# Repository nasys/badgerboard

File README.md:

___               _                      _                             _
				(  _`\            ( )                    ( )                           ( )
				| (_) )   _ _    _| |   __     __   _ __ | |_      _      _ _  _ __   _| |
				|  _ <' /'_` ) /'_` | /'_ `\ /'__`\( '__)| '_`\  /'_`\  /'_` )( '__)/'_` |
				| (_) )( (_| |( (_| |( (_) |(  ___/| |   | |_) )( (_) )( (_| || |  ( (_| |
			    (____/'`\__,_)`\__,_)`\__  |`\____)(_)   (_,__/'`\___/'`\__,_)(_)  `\__,_)
									 ( )_) |
								 	  \___/'
============================

### **Table of Contents**
 * [Prerequisites](#prerequisites)
 	* [Downloads](#downloads)
	* [General installation](#general-installation)
 	* [Mac OS X installation with Git](#mac-os-x-installation-with-git)
 	* [Windows installation with Git](#windows-installation-with-git)
 * [Badgerboard Setup](#badgerboard-setup)
	* [Test out your Badgerboard](#test-out-your-badgerboard) 
 	* [LoRa sensor setup](#lora-sensor-setup)
 * [Debugging](#debugging)
 * [Known issues](#known-issues)
 * [Version log](#version-log)
 * [Used libraries](#used-libraries)
 * [Licences](#licences)

### Prerequisites

##### Downloads

* [**Arduino**](https://www.arduino.cc/en/Main/Software)
* [**Git**](https://git-scm.com/book/en/v2/Getting-Started-Installing-Git)

#### General installation
* [Download](https://github.com/nasys/badgerboard/archive/master.zip) this library as **.zip** file

now this file is in downloads folder named Badgerboard-master.zip

* Open Arduino and include it under **Sketch -> Include library -> add .zip library**

##### Mac OS X installation with Git

* Open "**Finder**" (Press &#8984;+ Space ) 
* type in "terminal" and open it
* type "cd Documents/Arduino/libraries"
* type "git clone https://github.com/nasys/badgerboard"
* Now when you open up your Arduino and _Badgerboard_ library should appear under **Sketch -> Include library**

##### Windows installation with Git

Coming soon

### **Badgerboard setup**
#### Test out your Badgerboard
```diff
- DO NOT POWER ON WITHOUT ANTENNA! 

```

* Make sure Badgerboard power switch is turned ON ([button towards USB port](https://www.maker.io/-/media/makerio/makerimages/blogs/badgerboard/badgerboard-figure-1.jpg?la=en&hash=B2158C77D4DA2ACD35EAA878DF2E584F373AB571))
* connect Badgerboard to your PC/Mac 
* Open Arduino
* Open Blink example **Files -> Examples -> 01.Basics -> Blink**
* Make sure you have chosen correct board  **Tools -> Board -> LilyPad Arduino USB** and correct port **Tools -> Port** 
* Change the time(number in milliseconds) inside the brackets after "**delay**" to change the speed of blinking
* To **upload** click on the __right pointing arrow__ on the top-left corner of your Arduino window

In case all of this works then you have successfully uploaded your first program to Badgerboard

#### LoRa sensor setup

* Open **File -> Examples -> Badgerboard -> LoRa_temp_hum**
* Replace examples **devEUI**(16 hex char), **appEUI**(16 hex char) and **appKey**(32 hex char) with the ones that Your LoRaWAN™ solution provider has assigned.([example 1](#example-1)) 
* Upload Your code to Badgerboard

##### example 1

	In Arduino code your devEUI, appEUI and appKey are represented by char array and should look similar to 
	this example
	
	const uint8_t devEUI[8] = {
	0x11, 0x11, 0x22, 0x22,
	0x33, 0x33, 0x44, 0x44
	};

	const uint8_t appKey[16] = {
	0x11, 0x11, 0x11, 0x11,
	0x11, 0x11, 0x22, 0x22,
	0x22, 0x22, 0x22, 0x22,
	0x33, 0x33, 0x33, 0x33
	};

	const uint8_t appEUI[8] = {
	0x11, 0x22, 0x33, 0x44,
	0x55, 0x66, 0x77, 0x88
	};

### Debugging

To see Debugging messages open Serial Monitor **Tools -> Serial Monitor**
#### Known issues

* Take a look under [troubleshooting](https://github.com/nasys/badgerboard/wiki/Troubleshooting) page
* Works only with Arduino version 1.6.10 and later

### Version log

#### Version 0.0.3
	* Added a quickfix related to SF not changeing
	* Added _mod to library names to avoid issues if libraries are already installed
	
#### Version 0.0.2
:calendar:06.12.2016

	* Changed spreading factor changing to automatic
	* Added liquid detection example 

#### Version 0.0.1
:calendar:01.11.2016 

	Initial version of Badgerboard library

#### Used libraries
* [**FaBoHumidity_HTS221**](https://github.com/FaBoPlatform/FaBoHumidity-HTS221-Library)
* [**LowPower**](https://github.com/rocketscream/Low-Power)
* [**Sodaq_RN2483**](https://github.com/SodaqMoja/Sodaq_RN2483)

### **Licences**

All of the source files are distributed under the beerware license except where specified otherwise (i.e. external libraries)
 
#### Contacts
In case you found the instructions incomplete or have any questions regarding Badgerboard library
You can :
* Open new thread under [issues](https://github.com/nasys/badgerboard/issues)
* :e-mail: [contact us](mailto:badgerboard@nasys.no)

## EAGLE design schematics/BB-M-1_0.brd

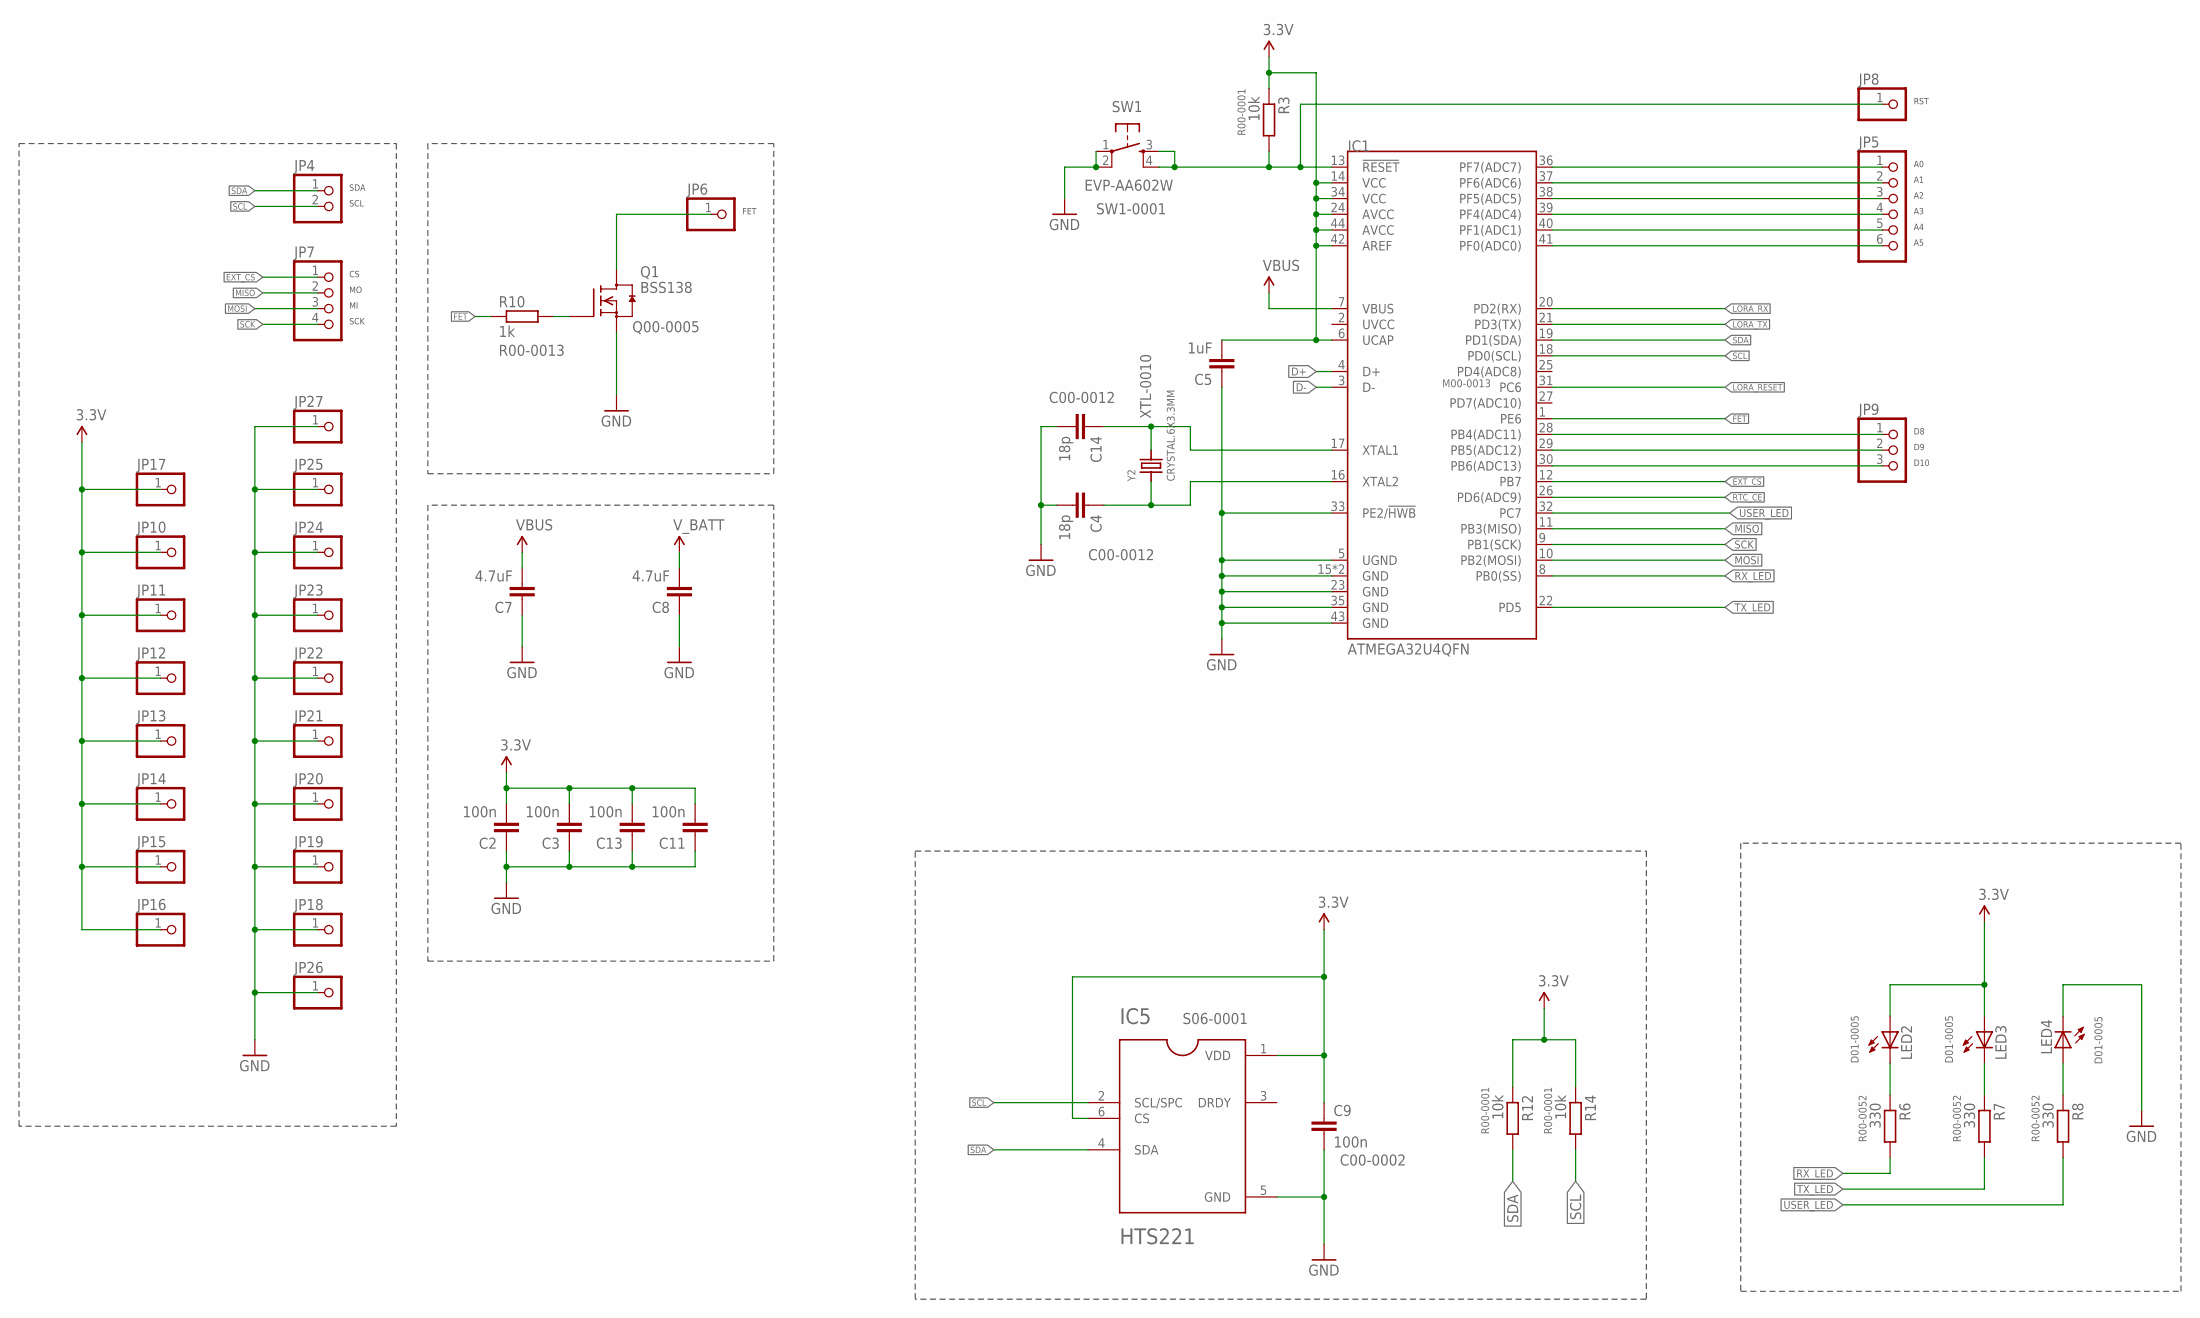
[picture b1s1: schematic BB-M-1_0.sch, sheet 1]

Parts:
C2, C3, C9, C11, C13: 100n; C0402
C4, C14: 18p; C0402
C5: 1uF; C0402
C7, C8: 4.7uF; C0603
IC1: ATMEGA32U4QFN; QFN-44
IC5: HTS221; LGA6R75P3X2_200X200X90
JP4: HEADER-1X2ROUND; 1X02_ROUND
JP5: HEADER-1X6ROUND; 1X06_ROUND
JP6, JP8, JP10, JP11, JP12, JP13, JP14, JP15, JP16, JP17, JP18, JP19, JP20, JP21, JP22, JP23, JP24, JP25, JP26, JP27: HEADER-1X1ROUND; 1X01_ROUND
JP7: HEADER-1X4ROUND; 1X04_ROUND
JP9: HEADER-1X3ROUND; 1X03_ROUND
LED2, LED3, LED4: LED0603; LED-0603
Q1: BSS138; SOT23
R3, R12, R14: 10k; R0402
R6, R7, R8: 330; R0402
R10: 1k; R0402
SW1: EVP-AA602W; UUS_BUTTON
Y2: CRYSTAL.6X3.3MM; 6X3.3MM

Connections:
3.3V: C2.2, C3.2, C5.2, C9.1, C11.2, C13.2, IC1.6 (UCAP), IC1.14 (VCC), IC1.24 (AVCC), IC1.34 (VCC), IC1.42 (AREF), IC1.44 (AVCC), IC5.1 (VDD), IC5.6 (CS), JP10.1, JP11.1, JP12.1, JP13.1, JP14.1, JP15.1, JP16.1, JP17.1, LED2.A, LED3.A, R3.1, R12.1, R14.1; also elsewhere on the board
5V: C7.2, IC1.7 (VBUS); also elsewhere on the board
D+: IC1.4 (D+); also elsewhere on the board
D-: IC1.3 (D-); also elsewhere on the board
EXT_CS: IC1.12 (PB7), JP7.1
FET: IC1.1 (PE6), R10.1
FET_OUTPUT: JP6.1, Q1.3 (D)
GND: C2.1, C3.1, C4.2, C5.1, C7.1, C8.1, C9.2, C11.1, C13.1, C14.2, IC1.5 (UGND), IC1.15 (GND), IC1.23 (GND), IC1.33 (PE2/!HWB), IC1.35 (GND), IC1.43 (GND), IC1.EPAD (GND), IC5.5 (GND), JP18.1, JP19.1, JP20.1, JP21.1, JP22.1, JP23.1, JP24.1, JP25.1, JP26.1, JP27.1, LED4.C, Q1.2 (S), SW1.1, SW1.2 (P1); also elsewhere on the board
LORA_RESET: IC1.31 (PC6); also elsewhere on the board
LORA_RX: IC1.20 (PD2(RX)); also elsewhere on the board
LORA_TX: IC1.21 (PD3(TX)); also elsewhere on the board
MISO: IC1.11 (PB3(MISO)), JP7.2
MOSI: IC1.10 (PB2(MOSI)), JP7.3
unnamed: LED2.C, R6.1
unnamed: C14.1, IC1.17 (XTAL1), Y2.2
unnamed: C4.1, IC1.16 (XTAL2), Y2.1
unnamed: IC1.30 (PB6(ADC13)), JP9.3
unnamed: IC1.29 (PB5(ADC12)), JP9.2
unnamed: Q1.1 (G), R10.2
unnamed: IC1.36 (PF7(ADC7)), JP5.1
unnamed: IC1.41 (PF0(ADC0)), JP5.6
unnamed: IC1.40 (PF1(ADC1)), JP5.5
unnamed: IC1.39 (PF4(ADC4)), JP5.4
unnamed: IC1.38 (PF5(ADC5)), JP5.3
unnamed: LED4.A, R8.1
unnamed: LED3.C, R7.1
unnamed: IC1.37 (PF6(ADC6)), JP5.2
unnamed: IC1.28 (PB4(ADC11)), JP9.1
RESET: IC1.13 (!RESET), JP8.1, R3.2, SW1.3 (S), SW1.4 (S1)
RTC_CE: IC1.26 (PD6(ADC9))
RX_LED: IC1.8 (PB0(SS)), R6.2
SCK: IC1.9 (PB1(SCK)), JP7.4
SCL: IC1.18 (PD0(SCL)), IC5.2 (SCL/SPC), JP4.2, R14.2
SDA: IC1.19 (PD1(SDA)), IC5.4 (SDA), JP4.1, R12.2
TX_LED: IC1.22 (PD5), R7.2
USER_LED: IC1.32 (PC7), R8.2
V_BATT: C8.2; also elsewhere on the board

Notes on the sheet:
SDA
SCL
SCK
FET
RST
D10

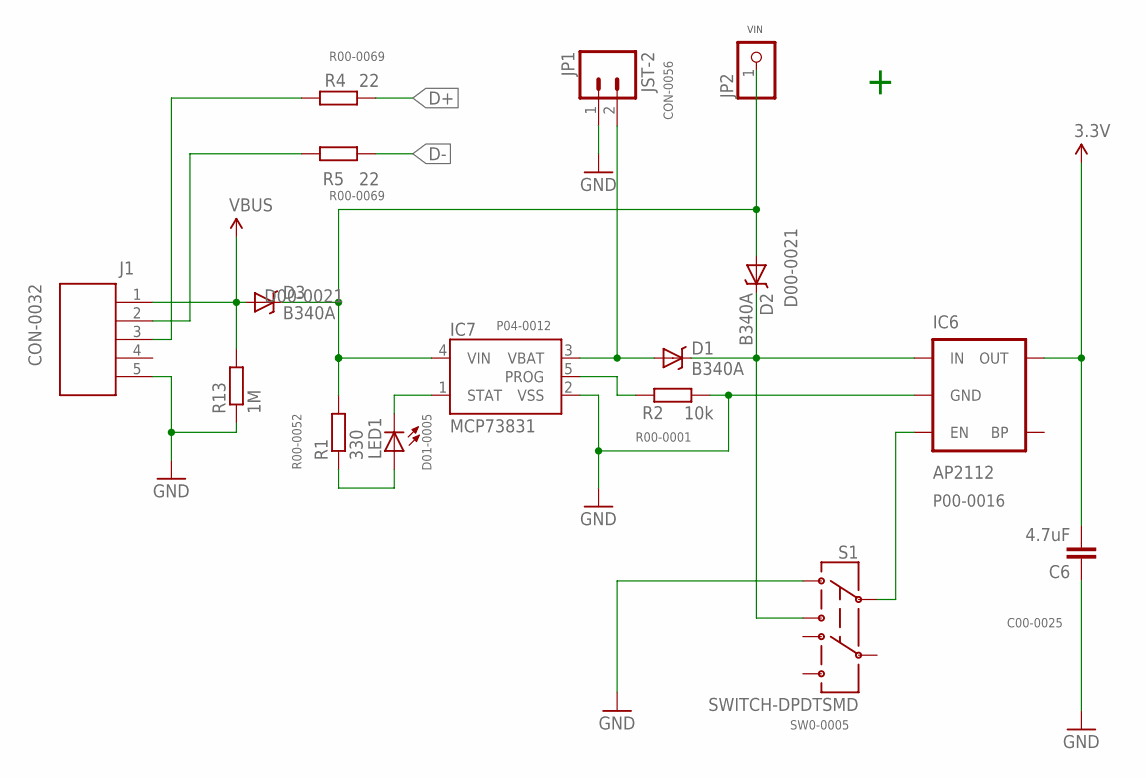
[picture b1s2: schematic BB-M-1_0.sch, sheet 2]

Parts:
C6: 4.7uF; C0603
D1, D2, D3: B340A; SMA-DIODE
IC6: AP2112; SOT23-5
IC7: MCP73831; SOT23-5
J1: 629105136821
JP1: JST-2; JST-2-SMD
JP2: PINHD-1X1CB; 1X01-CLEANBIG
LED1: LED0603; LED-0603
R1: 330; R0402
R2: 10k; R0402
R4, R5: 22; R0402
R13: 1M; R0402
S1: SWITCH-DPDTSMD; AYZ0202

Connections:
3.3V: C6.2, IC6.5 (OUT); also elsewhere on the board
5V: D3.A, J1.1, R13.2; also elsewhere on the board
D+: R4.1; also elsewhere on the board
D-: R5.1; also elsewhere on the board
GND: C6.1, IC6.2 (GND), IC7.2 (VSS), J1.5, JP1.1 (2), R2.1, R13.1, S1.1; also elsewhere on the board
unnamed: D1.C, D2.C, IC6.1 (IN), S1.3
unnamed: LED1.A, R1.1
unnamed: IC7.1 (STAT), LED1.C
unnamed: IC7.5 (PROG), R2.2
unnamed: IC6.3 (EN), S1.2
unnamed: J1.2, R5.2
unnamed: J1.3, R4.2
unnamed: D2.A, D3.C, IC7.4 (VIN), JP2.1, R1.2
V_BATT: D1.A, IC7.3 (VBAT), JP1.2 (1); also elsewhere on the board

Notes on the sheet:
VIN

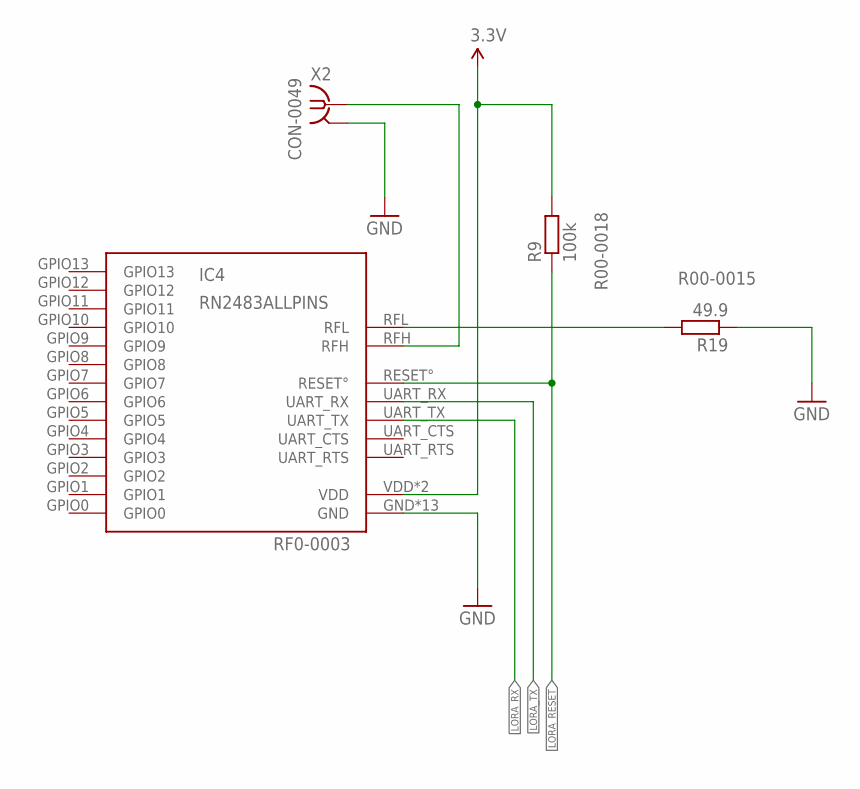
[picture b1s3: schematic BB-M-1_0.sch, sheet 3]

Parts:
IC4: RN2483ALLPINS; RN2483
R9: 100k; R0402
R19: 49.9; R0402
X2: 132414

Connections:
3.3V: IC4.VDD, IC4.VDD2 (VDD), R9.2; also elsewhere on the board
GND: IC4.GND, IC4.GND1 (GND), IC4.GND2 (GND), IC4.GND3 (GND), IC4.GND4 (GND), IC4.GND5 (GND), IC4.GND6 (GND), IC4.GND7 (GND), IC4.GND8 (GND), IC4.GND9 (GND), IC4.GND10 (GND), IC4.GND11 (GND), IC4.GND12 (GND), R19.1, X2.G@1 (GND), X2.G@2 (GND), X2.G@3 (GND), X2.G@4 (GND); also elsewhere on the board
LORA_RESET: IC4.RESET°, R9.1; also elsewhere on the board
LORA_RX: IC4.UART_TX; also elsewhere on the board
LORA_TX: IC4.UART_RX; also elsewhere on the board
unnamed: IC4.RFL, R19.2
unnamed: IC4.RFH, X2.1

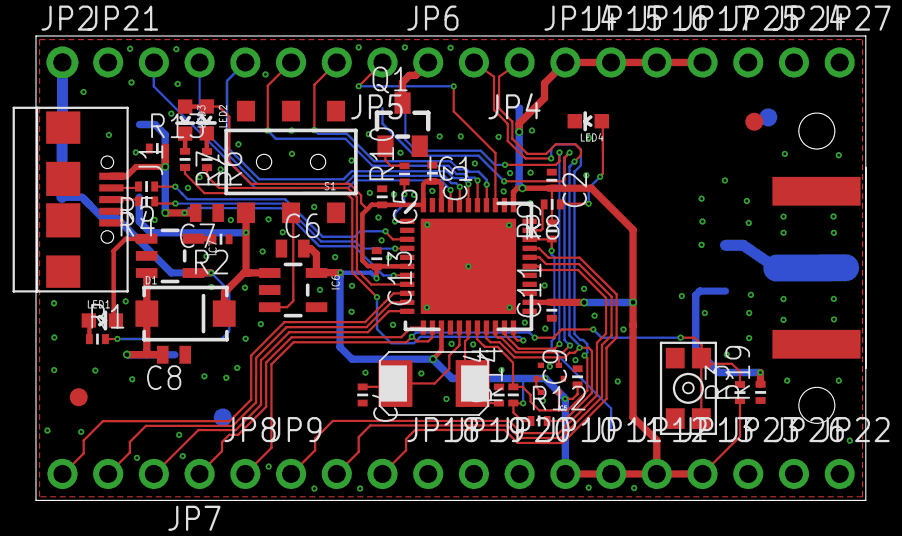
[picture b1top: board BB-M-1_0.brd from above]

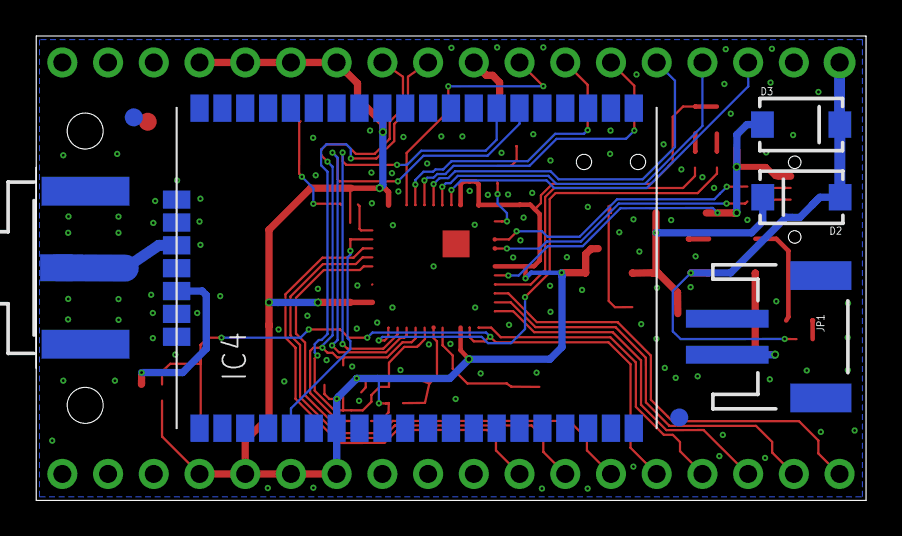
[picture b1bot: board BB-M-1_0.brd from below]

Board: 2 copper layers, 46.1 x 25.8 mm, 73 parts (7 on the bottom side), 46 nets.

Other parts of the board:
U$1, U$2, U$3, U$4: FIDUCIAL_L10

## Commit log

2016-10-24 made few changes
2016-10-24 changed readme file
2016-10-24 moved all to one folder
2016-11-01 added gitignore ??
2016-11-01 gitignore
2016-11-01 edited gitignore
2016-11-01 master push
2016-11-01 readme
2016-11-01 readme file
2016-11-01 added version 0.0.1
2016-11-22 canges to readme file
2016-11-22 deleted unnecessary files and added know issues to readme file
2016-11-22 changed .gitignore
2016-11-22 deleted DS_Store files
2016-11-30 liquid_sensor example
2016-12-02 trying out new readme style
2016-12-06 all changes marked under version 0.0.2 in readme
2016-12-08 readme file test
2016-12-08 external links open new tab
2016-12-08 links
2016-12-13 API changes. Refactoring.
2016-12-13 changed no_ack to regular
2017-01-11 initial sf branch
2017-01-17 Bare channel interface.
2017-01-31 abp test
2017-02-08 added _mod to library names
2017-02-08 removed workspace files and CMWX files
2017-02-08 deleted unnecessary files
2017-02-21 Move to schematics
2017-02-27 sf change example
2017-02-28 pdf test
2017-02-28 pdf file
2017-03-31 initial cayenne branch
2017-05-25 fixed wdt timing issue
2017-05-30 changes with .h file
2017-10-09 png test
2017-10-09 png file
2017-11-22 changed adr in init functions to variables instead of fixed values

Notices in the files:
parts and their libraries:
SparkFun-DigitalIC: Licensing: CC v3.0 Share-Alike You are welcome to use this library for commercial purposes.
MAX9812: License : GNU General Public License version 2 (see bottom)
EAGLE-INPUT_OUTPUT_CONNECTORS-rev1: Copyright: Würth Elektronik
